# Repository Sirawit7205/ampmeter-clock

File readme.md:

# Ammeter Clock Controller

This is an open-source KiCAD 5 design files for a logic chips-driven clock that output time on three ammeters.

## Pictures

## Features

This is a unique clock that will certainly impress people around you.

- Ammeter Output
	- Shows hour, minute, and second on three ammeters.
	- Works with both analog and digital meters.
- Quartz Crystal-driven Clock with CD4060 IC
- Design with logic ICs. Only need 11 chips for the circuit to work.
- Set Hour, Set Min, Reset, and Clock Halt buttons
- Ammeter adjustment trimpots
- Aluminum Front Panel design available [here](https://github.com/Sirawit7205/ammeter-clock-frontpanel)

## Revisions

We are currently at Revision 2. Changelog is below:

**Revision 1 (July 2021)**
- Initial Design
- H and M buttons are swapped.

**Revision 2 (September 2021)**
- Fix H and M buttons.

## What is provided

The goal of this repository is to enable you to build this on your own as easy as possible. **The schematics, PCB design, and an interactive BOM are provided.**

Hardware is licensed under `SPDX-License-Identifier: CERN-OHL-S-2.0`

Contains no software

Documentation is licensed under `SPDX-License-Identifier: CC-BY-SA-4.0`

## Ordering

You can export gerbers from this project and order the board yourself.

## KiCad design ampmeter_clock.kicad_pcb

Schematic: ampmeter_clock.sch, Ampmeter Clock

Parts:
C1, C2, C3, C4, C5, C6, C7, C8, C9, C10, C11: 100nF; C_0603_1608Metric
C12, C13: 22pF; C_0603_1608Metric
C14, C15, C16: 1uF; C_0603_1608Metric
C17: 470uF; CP_Radial_D8.0mm_P3.50mm
D1: ZMM6V2; D_MiniMELF
D2, D3, D4, D5, D6, D7: 1N4148; D_MiniMELF
D8, D9, D10, D11, D12, D13, D14, D15, D16, D17, D18, D19, D20, D21, D22, D23, D24, D25, D26, D27: LED; LED_0603_1608Metric
J1: Barrel_Jack_Switch; BarrelJack_Horizontal
MES1: HOUR; TerminalBlock_bornier-2_P5.08mm
MES2: MINUTE; TerminalBlock_bornier-2_P5.08mm
MES3: SECOND; TerminalBlock_bornier-2_P5.08mm
Q1, Q2, Q3, Q4, Q5, Q6, Q7, Q8, Q9, Q10, Q11, Q12, Q13, Q14, Q15, Q16, Q17, Q18, Q19: 2N7002; SOT-23
Q20: NCE30P12S; SOIC-8_3.9x4.9mm_P1.27mm
R1, R2, R3, R8, R16, R20, R24, R25, R30: 4k7; R_0603_1608Metric
R4: 470k; R_0603_1608Metric
R5, R6, R7, R13, R14, R15, R21, R22, R23, R26, R27, R28, R31, R32, R33, R34, R35, R36, R37: 100R; R_0603_1608Metric
R9: 10M; R_0805_2012Metric
R10, R11, R12: 2k2; R_0603_1608Metric
R17, R18, R19: 1k; R_0603_1608Metric
R29: 4K7; R_0603_1608Metric
R38: 100k; R_0603_1608Metric
RN1, RN2, RN3, RN4, RN5, RN6: 4k7; R_Array_Convex_4x0603
RV1, RV2, RV3, RV4, RV5, RV6, RV7, RV8, RV9, RV10, RV11, RV12, RV13, RV14, RV15, RV16, RV17, RV18, RV19: 1k; 3362P_1
SW1: SET_HOUR; TS-1101
SW2: SET_MIN; TS-1101
SW3: RESET; TS-1101
SW4: CLK_HALT; TS-1101
U1: 4027; DIP-16_W7.62mm
U2, U3: 40106; DIP-14_W7.62mm
U4, U5: 4081; DIP-14_W7.62mm
U6: 4060; DIP-16_W7.62mm
U7, U9: 4510; DIP-16_W7.62mm
U8, U10, U11: 4516; DIP-16_W7.62mm
Y1: 32.768kHz; Crystal_Round_D2.0mm_Vertical

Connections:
+5V: C1.1, C2.1, C3.1, C4.1, C5.1, C6.1, C7.1, C8.1, C9.1, C10.1, C11.1, C17.1, D1.1 (K), MES1.2 (+), MES2.2 (+), MES3.2 (+), Q20.1, Q20.2, Q20.3, R16.1, R24.1, SW1.1, SW2.1, SW3.1, SW4.1, U1.5 (K), U1.6 (J), U1.16 (VDD), U2.14 (VDD), U3.14 (VDD), U4.14 (VDD), U5.14 (VDD), U6.16 (VDD), U7.10 (U/D), U7.16 (VDD), U8.10 (U/D), U8.16 (VDD), U9.10 (U/D), U9.16 (VDD), U10.10 (U/D), U10.16 (VDD), U11.10 (U/D), U11.16 (VDD)
CLK: D13.2, U1.1 (Q), U1.13 (C), U7.15 (CLK), U8.15 (CLK), U9.15 (CLK), U10.15 (CLK), U11.15 (CLK)
GND: C1.2, C2.2, C3.2, C4.2, C5.2, C6.2, C7.2, C8.2, C9.2, C10.2, C11.2, C12.2, C13.2, C14.2, C15.2, C16.2, C17.2, D1.2 (A), J1.2, Q1.2, Q2.2, Q3.2, Q4.2, Q5.2, Q6.2, Q7.2, Q8.2, Q9.2, Q10.2, Q11.2, Q12.2, Q13.2, Q14.2, Q15.2, Q16.2, Q17.2, Q18.2, Q19.2, R8.2, R20.2, R25.2, R29.2, R30.2, R38.2, RN1.5, RN1.6, RN1.7, RN1.8, RN2.5, RN2.6, RN2.7, RN2.8, RN3.5, RN3.6, RN3.7, RN3.8, RN4.5, RN4.6, RN4.7, RN4.8, RN5.5, RN5.6, RN5.7, RN5.8, RN6.5, RN6.6, RN6.7, RN6.8, U1.4 (R), U1.7 (S), U1.8 (VSS), U1.9 (S), U1.11 (K), U2.7 (VSS), U2.13, U3.3, U3.7 (VSS), U3.9, U4.7 (VSS), U5.7 (VSS), U6.8 (VSS), U7.1 (PE), U7.3 (A4), U7.4 (A1), U7.5 (CI), U7.8 (VSS), U7.12 (A2), U7.13 (A3), U8.3 (A4), U8.4 (A1), U8.8 (VSS), U8.12 (A2), U8.13 (A3), U9.1 (PE), U9.3 (A4), U9.4 (A1), U9.8 (VSS), U9.12 (A2), U9.13 (A3), U10.3 (A4), U10.4 (A1), U10.8 (VSS), U10.12 (A2), U10.13 (A3), U11.3 (A4), U11.4 (A1), U11.8 (VSS), U11.12 (A2), U11.13 (A3)
HOUR_0: D8.2, R5.2, U11.6 (Q1)
HOUR_1: D9.2, R13.2, U11.11 (Q2)
HOUR_2: D10.2, R21.2, U11.14 (Q3)
HOUR_3: D11.2, R26.2, U4.12, U11.2 (Q4)
HOUR_4: D12.2, R31.2, U1.15 (Q), U5.13
MIN_0: D14.2, R6.2, U9.6 (Q1)
MIN_1: D15.2, R14.2, U9.11 (Q2)
MIN_2: D16.2, R22.2, U9.14 (Q3)
MIN_3: D17.2, R27.2, U9.2 (Q4)
MIN_4: D18.2, R32.2, U5.1, U10.6 (Q1)
MIN_5: D19.2, R34.2, U5.9, U10.11 (Q2)
MIN_6: D20.2, R36.2, U5.2, U5.8, U10.14 (Q3)
unnamed: C12.1, R4.2, Y1.1
unnamed: C13.1, R9.2, U6.11 (OSCIN), Y1.2
unnamed: C14.1, R20.1, SW1.2, U3.5
unnamed: C15.1, R25.1, SW2.2, U3.1
unnamed: C16.1, R30.1, SW3.2, U3.13
unnamed: D2.1 (K), U3.2
unnamed: D4.1 (K), U3.6
unnamed: D6.1 (K), D7.1 (K), R29.1, U1.12 (R)
unnamed: D8.1, RN1.1
unnamed: D9.1, RN1.2
unnamed: D10.1, RN1.3
unnamed: D11.1, RN1.4
unnamed: D12.1, RN2.1
unnamed: D13.1, RN2.4
unnamed: D14.1, RN3.1
unnamed: D15.1, RN3.2
unnamed: D16.1, RN3.3
unnamed: D17.1, RN3.4
unnamed: D18.1, RN4.1
unnamed: D19.1, RN4.2
unnamed: D20.1, RN4.3
unnamed: D21.1, RN5.1
unnamed: D22.1, RN5.2
unnamed: D23.1, RN5.3
unnamed: D24.1, RN5.4
unnamed: D25.1, RN6.1
unnamed: D26.1, RN6.2
unnamed: D27.1, RN6.3
unnamed: J1.1, Q20.5, Q20.6, Q20.7, Q20.8
unnamed: MES1.1 (-), RV1.3, RV4.3, RV7.3, RV10.3, RV13.3
unnamed: MES2.1 (-), RV2.3, RV5.3, RV8.3, RV11.3, RV14.3, RV16.3, RV18.3
unnamed: MES3.1 (-), RV3.3, RV6.3, RV9.3, RV12.3, RV15.3, RV17.3, RV19.3
unnamed: Q1.1, R5.1
unnamed: Q1.3, R1.2
unnamed: Q2.1, R6.1
unnamed: Q2.3, R2.2
unnamed: Q3.1, R7.1
unnamed: Q3.3, R3.2
unnamed: Q4.1, R13.1
unnamed: Q4.3, R10.2
unnamed: Q5.1, R14.1
unnamed: Q5.3, R11.2
unnamed: Q6.1, R15.1
unnamed: Q6.3, R12.2
unnamed: Q7.1, R21.1
unnamed: Q7.3, R17.2
unnamed: Q8.1, R22.1
unnamed: Q8.3, R18.2
unnamed: Q9.1, R23.1
unnamed: Q9.3, R19.2
unnamed: Q10.1, R26.1
unnamed: Q10.3, RV10.1, RV10.2
unnamed: Q11.1, R27.1
unnamed: Q11.3, RV11.1, RV11.2
unnamed: Q12.1, R28.1
unnamed: Q12.3, RV12.1, RV12.2
unnamed: Q13.1, R31.1
unnamed: Q13.3, RV13.1, RV13.2
unnamed: Q14.1, R32.1
unnamed: Q14.3, RV14.1, RV14.2
unnamed: Q15.1, R33.1
unnamed: Q15.3, RV15.1, RV15.2
unnamed: Q16.1, R34.1
unnamed: Q16.3, RV16.1, RV16.2
unnamed: Q17.1, R35.1
unnamed: Q17.3, RV17.1, RV17.2
unnamed: Q18.1, R36.1
unnamed: Q18.3, RV18.1, RV18.2
unnamed: Q19.1, R37.1
unnamed: Q19.3, RV19.1, RV19.2
unnamed: Q20.4, R38.1
unnamed: R1.1, RV1.1, RV1.2
unnamed: R2.1, RV2.1, RV2.2
unnamed: R3.1, RV3.1, RV3.2
unnamed: R4.1, R9.1, U6.10 (OSCRES)
unnamed: R8.1, SW4.2, U6.12 (RST)
unnamed: R10.1, RV4.1, RV4.2
unnamed: R11.1, RV5.1, RV5.2
unnamed: R12.1, RV6.1, RV6.2
unnamed: R17.1, RV7.1, RV7.2
unnamed: R18.1, RV8.1, RV8.2
unnamed: R19.1, RV9.1, RV9.2
unnamed: U1.3 (C), U6.3 (Q14)
unnamed: U1.10 (J), U2.10
unnamed: U2.1, U7.7 (CO), U8.5 (CI)
unnamed: U2.2, U4.5
unnamed: U2.3, U4.4
unnamed: U2.6, U5.5
unnamed: U2.9, U5.4
unnamed: U3.11, U3.12
unnamed: U4.3, U4.6
unnamed: U4.11, U5.12
unnamed: U5.3, U5.6
unnamed: U2.5, U9.7 (CO), U10.5 (CI)
unnamed: U2.11, U4.13, U11.7 (CO)
RST: D7.2 (A), U3.10, U7.9 (RST), U8.9 (RST), U9.9 (RST), U10.9 (RST), U11.9 (RST)
RST_STAGE1: U4.10, U8.1 (PE)
RST_STAGE2: U5.10, U10.1 (PE)
RST_STAGE3: D6.2 (A), U5.11, U11.1 (PE)
SEC_0: D21.2, R7.2, U7.6 (Q1)
SEC_1: D22.2, R15.2, U7.11 (Q2)
SEC_2: D23.2, R23.2, U7.14 (Q3)
SEC_3: D24.2, R28.2, U7.2 (Q4)
SEC_4: D25.2, R33.2, U4.1, U8.6 (Q1)
SEC_5: D26.2, R35.2, U4.9, U8.11 (Q2)
SEC_6: D27.2, R37.2, U4.2, U4.8, U8.14 (Q3)
~CI_STAGE2: D2.2 (A), D3.2 (A), R16.2, U9.5 (CI)
~CI_STAGE3: D4.2 (A), D5.2 (A), R24.2, U11.5 (CI)
~CO_STAGE1: D3.1 (K), U2.4
~CO_STAGE2: D5.1 (K), U2.8

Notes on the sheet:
Upper - Fixed Middle - Nothing Lower - Momentary
Clock Source
Time Set Buttons
Sec Counter
Min Counter
Hour Counter
Power Units
Unused Units
Output Stages
Decoupling Capacitors
Power
Output Indicators
RE1CM471F12PT

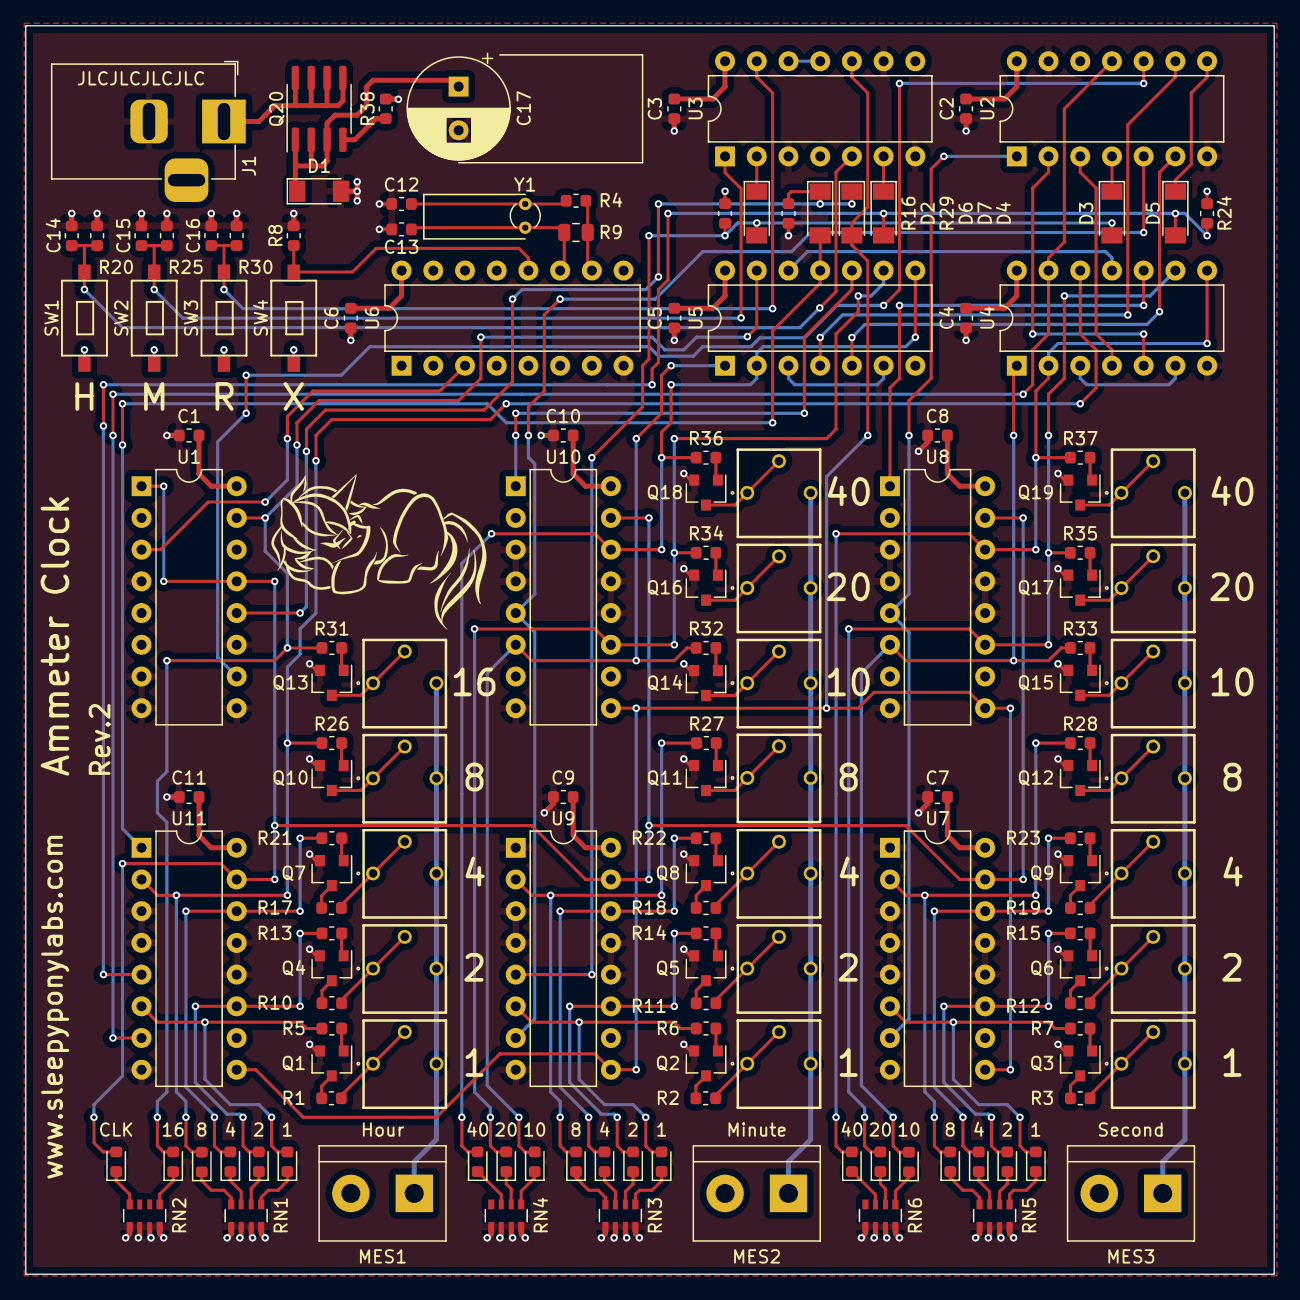
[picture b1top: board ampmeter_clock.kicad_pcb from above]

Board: 4 copper layers, 100.0 x 100.0 mm, 147 parts (0 on the bottom side), 125 nets.

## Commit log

2021-03-12 Add .gitignore
2021-06-16 Fix bugs
2021-06-19 Component Placement
2021-07-01 PCB done
2021-07-17 Fix PCB Edge, add ibom
2021-09-08 Fixed symbol lib path
2021-09-08 Fix swapped H and M buttons and misc traces adjustments
2023-06-16 Update schematics PDF
2023-07-18 Fix silk, generate ibom for rev 2
2023-07-18 Add license, readme, and pics
